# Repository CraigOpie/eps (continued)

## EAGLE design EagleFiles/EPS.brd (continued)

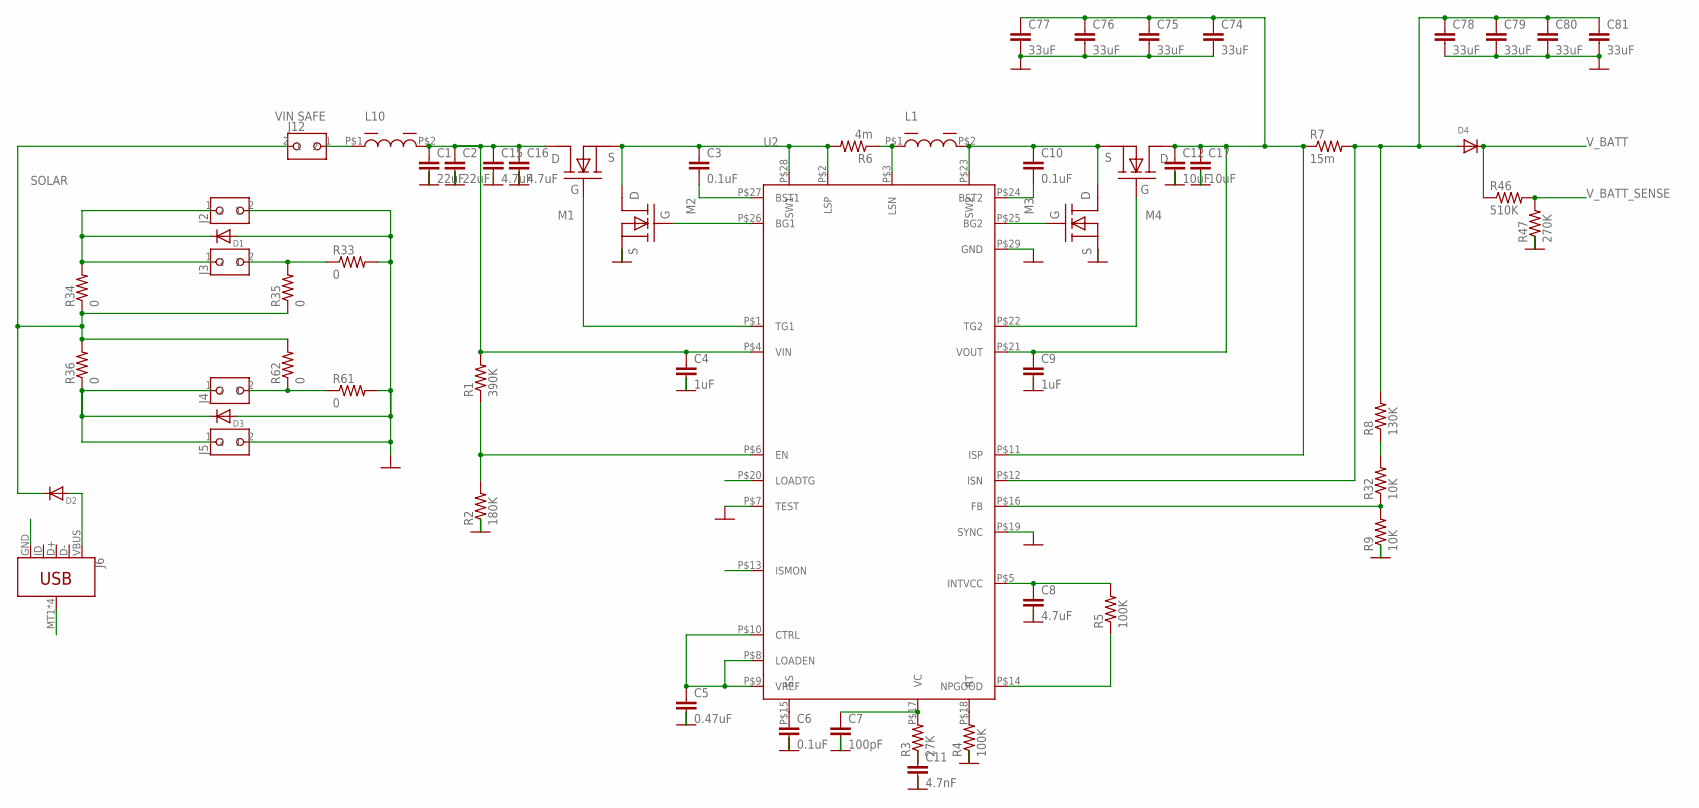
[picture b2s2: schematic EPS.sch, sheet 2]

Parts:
C1, C2: 22uF; 0805
C3, C6, C10: 0.1uF; 0805
C4, C9: 1uF; 0805
C5: 0.47uF; 0805
C7: 100pF; 0805
C8, C15, C16: 4.7uF; 0805
C11: 4.7nF; 0805
C12, C17: 10uF; 0805
C74, C75, C76, C77, C78, C79, C80, C81: 33uF; 1206
D1, D2, D3, D4: DIODE_SOD-123FL; SOD-123FL
J2, J3, J4, J5, J12: 2PIN_HEADER; 2MM_2PIN_HEADER
J6: USB_MICRO-B_SMT; USB-MICROB
L1, L10: 6uH; 7443551600
M1, M2: BSZ100N06LS3
M3, M4: BSZ033NE2LS5; BSZ100N06LS3
R1: 390K; 0805
R2: 180K; 0805
R3: 27K; 0805
R4, R5: 100K; 0805
R6: 4m; 0805
R7: 15m; 0805
R8: 130K; 0805
R9, R32: 10K; 0805
R33, R34, R35, R36, R61, R62: 0; 0603-RES
R46: 510K; 0805
R47: 270K; 0805
U2: LT8390UFD

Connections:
GND: C1.2, C2.2, C4.2, C5.2, C6.2, C7.2, C8.2, C9.2, C11.2, C12.2, C15.2, C16.2, C17.2, C74.2, C75.2, C76.2, C77.2, C78.2, C79.2, C80.2, C81.2, D1.A, D3.A, J2.2, J5.2, J6.GND, J6.MT1 (SHIELD), J6.MT2 (SHIELD), J6.P$1 (SHIELD), J6.P$2 (SHIELD), M2.P$2 (S), M2.P$3 (S), M2.P$4 (S), M3.P$2 (S), M3.P$3 (S), M3.P$4 (S), R2.1, R4.1, R9.1, R33.2, R47.1, R61.2, U2.P$7 (TEST), U2.P$19 (SYNC), U2.P$29 (GND); also elsewhere on the board
unnamed: C3.1, M1.P$2 (S), M1.P$3 (S), M1.P$4 (S), M2.P$5 (D), M2.P$6 (D), M2.P$7 (D), M2.P$8 (D), M2.P$9 (D), R6.2, U2.P$2 (LSP), U2.P$28 (SW1)
unnamed: C3.2, U2.P$27 (BST1)
unnamed: R8.1, R32.2
unnamed: M2.P$1 (G), U2.P$26 (BG1)
unnamed: M1.P$1 (G), U2.P$1 (TG1)
unnamed: M3.P$1 (G), U2.P$25 (BG2)
unnamed: R1.1, R2.2, U2.P$6 (EN)
unnamed: C5.1, U2.P$8 (LOADEN), U2.P$9 (VREF), U2.P$10 (CTRL)
unnamed: C6.1, U2.P$15 (SS)
unnamed: C7.1, R3.2, U2.P$17 (VC)
unnamed: R4.2, U2.P$18 (RT)
unnamed: R5.1, U2.P$14 (NPGOOD)
unnamed: C8.1, R5.2, U2.P$5 (INTVCC)
unnamed: L1.P$1, R6.1, U2.P$3 (LSN)
unnamed: C10.1, L1.P$2, M3.P$5 (D), M3.P$6 (D), M3.P$7 (D), M3.P$8 (D), M3.P$9 (D), M4.P$2 (S), M4.P$3 (S), M4.P$4 (S), U2.P$23 (SW2)
unnamed: C10.2, U2.P$24 (BST2)
unnamed: C9.1, C12.1, C17.1, C74.1, C75.1, C76.1, C77.1, M4.P$5 (D), M4.P$6 (D), M4.P$7 (D), M4.P$8 (D), M4.P$9 (D), R7.1, U2.P$11 (ISP), U2.P$21 (VOUT)
unnamed: M4.P$1 (G), U2.P$22 (TG2)
unnamed: J12.1, L10.P$1
unnamed: R9.2, R32.1, U2.P$16 (FB)
unnamed: D1.C, J2.1, J3.1, R34.2
unnamed: J3.2, R33.1, R35.2
unnamed: C11.1, R3.1
unnamed: J4.2, R61.1, R62.1
unnamed: D2.A, J6.VBUS
unnamed: C1.1, C2.1, C4.1, C15.1, C16.1, L10.P$2, M1.P$5 (D), M1.P$6 (D), M1.P$7 (D), M1.P$8 (D), M1.P$9 (D), R1.2, U2.P$4 (VIN)
unnamed: D3.C, J4.1, J5.1, R36.1
SOLAR: D2.C, J12.2, R34.1, R35.1, R36.2, R62.2
V_BATT: C78.1, C79.1, C80.1, C81.1, D4.A, D4.C, R7.2, R8.2, R46.1, U2.P$12 (ISN); also elsewhere on the board
V_BATT_SENSE: R46.2, R47.2; also elsewhere on the board

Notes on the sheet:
VIN SAFE

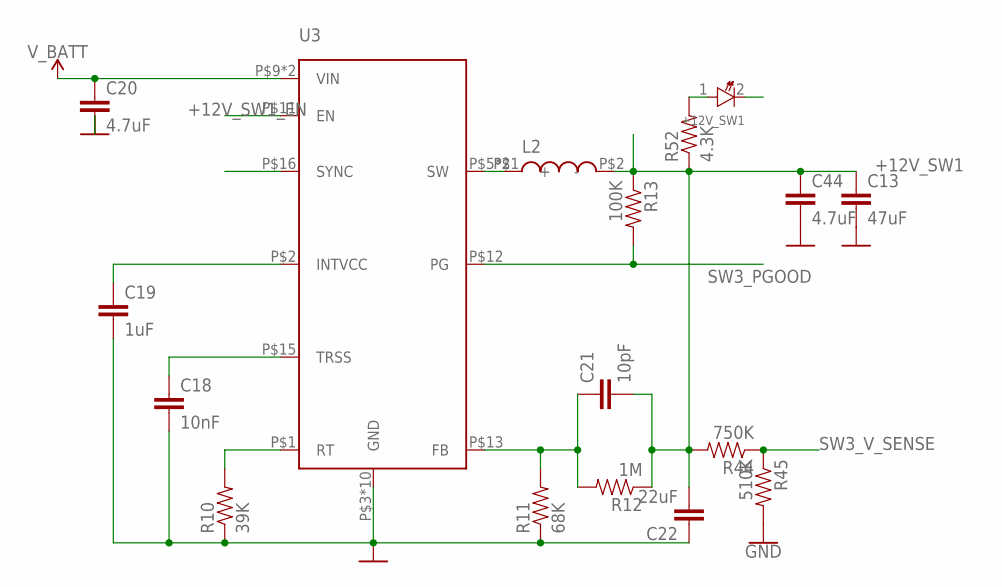
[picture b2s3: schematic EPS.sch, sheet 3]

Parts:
+12V_SW1: LED_0805
C13: 47uF; 1206
C18: 10nF; 0805
C19: 1uF; 0805
C20, C44: 4.7uF; 0805
C21: 10pF; 0805
C22: 22uF; 0805
L2: 10uH; XAL4040-103ME
R10: 39K; 0805
R11: 68K; 0805
R12: 1M; 0805
R13: 100K; 0805
R44: 750K; 0805
R45: 510K; 0805
R52: 4.3K; 0805
U3: LT8609S

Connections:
+12V_SW1: C13.1, C21.2, C22.2, C44.1, L2.P$2 (-), R12.1, R13.1, R44.2, R52.1; also elsewhere on the board
+12V_SW1_EN: U3.P$11 (EN); also elsewhere on the board
GND: +12V_SW1.2, C13.2, C18.2, C19.2, C20.2, C22.1, C44.2, R10.1, R11.1, R45.2, U3.P$3 (GND), U3.P$4 (GND), U3.P$7 (GND), U3.P$8 (GND), U3.P$14 (GND), U3.P$17 (GND), U3.P$18 (GND), U3.P$19 (GND), U3.P$20 (GND), U3.P$21 (GND); also elsewhere on the board
unnamed: L2.P$1 (+), U3.P$5 (SW), U3.P$6 (SW)
unnamed: R10.2, U3.P$1 (RT)
unnamed: C21.1, R11.2, R12.2, U3.P$13 (FB)
unnamed: C19.1, U3.P$2 (INTVCC)
unnamed: C18.1, U3.P$15 (TRSS)
unnamed: +12V_SW1.1, R52.2
SW3_PGOOD: R13.2, U3.P$12 (PG)
SW3_V_SENSE: R44.1, R45.1; also elsewhere on the board
V_BATT: C20.1, U3.P$9 (VIN), U3.P$10 (VIN); also elsewhere on the board

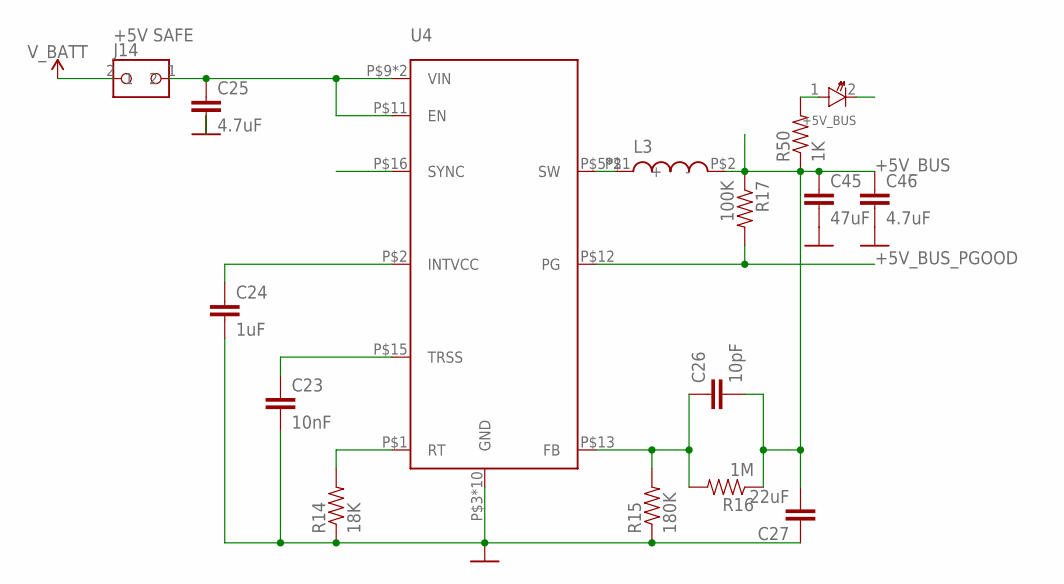
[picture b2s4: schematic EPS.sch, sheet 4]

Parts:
+5V_BUS: LED_0805
C23: 10nF; 0805
C24: 1uF; 0805
C25, C46: 4.7uF; 0805
C26: 10pF; 0805
C27: 22uF; 0805
C45: 47uF; 0805
J14: 2PIN_HEADER; 2MM_2PIN_HEADER
L3: 2.2uH; XAL4040-103ME
R14: 18K; 0805
R15: 180K; 0805
R16: 1M; 0805
R17: 100K; 0805
R50: 1K; 0805
U4: LT8609S

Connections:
+5V_BUS: C26.2, C27.2, C45.1, C46.1, L3.P$2 (-), R16.1, R17.1, R50.1; also elsewhere on the board
+5V_BUS_PGOOD: R17.2, U4.P$12 (PG)
GND: +5V_BUS.2, C23.2, C24.2, C25.2, C27.1, C45.2, C46.2, R14.1, R15.1, U4.P$3 (GND), U4.P$4 (GND), U4.P$7 (GND), U4.P$8 (GND), U4.P$14 (GND), U4.P$17 (GND), U4.P$18 (GND), U4.P$19 (GND), U4.P$20 (GND), U4.P$21 (GND); also elsewhere on the board
unnamed: R14.2, U4.P$1 (RT)
unnamed: C26.1, R15.2, R16.2, U4.P$13 (FB)
unnamed: C24.1, U4.P$2 (INTVCC)
unnamed: C23.1, U4.P$15 (TRSS)
unnamed: L3.P$1 (+), U4.P$5 (SW), U4.P$6 (SW)
unnamed: +5V_BUS.1, R50.2
V_BATT: J14.2; also elsewhere on the board
V_BUS: C25.1, J14.1, U4.P$9 (VIN), U4.P$10 (VIN), U4.P$11 (EN); also elsewhere on the board

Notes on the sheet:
+5V SAFE

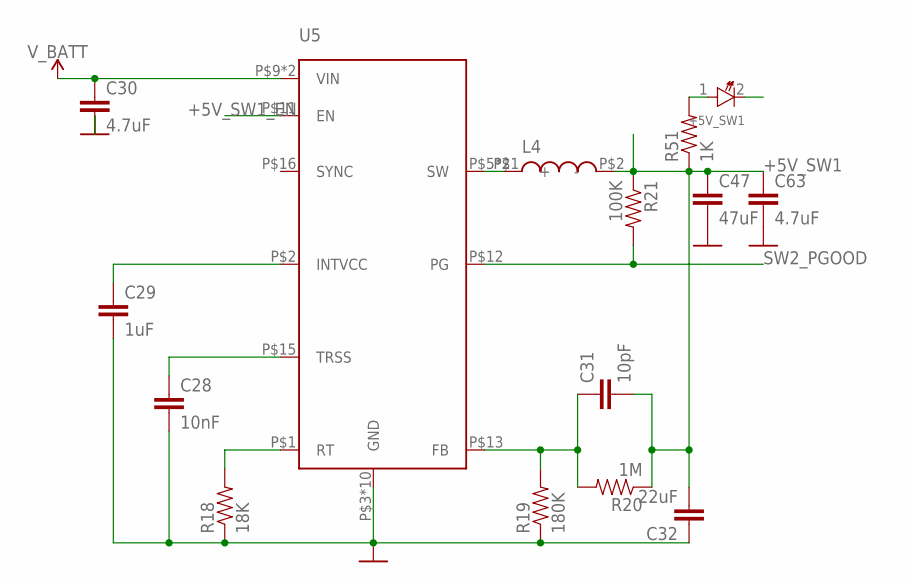
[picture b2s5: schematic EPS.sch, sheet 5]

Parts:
+5V_SW1: LED_0805
C28: 10nF; 0805
C29: 1uF; 0805
C30, C63: 4.7uF; 0805
C31: 10pF; 0805
C32: 22uF; 0805
C47: 47uF; 0805
L4: 2.2uH; XAL4040-103ME
R18: 18K; 0805
R19: 180K; 0805
R20: 1M; 0805
R21: 100K; 0805
R51: 1K; 0805
U5: LT8609S

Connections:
+5V_SW1: C31.2, C32.2, C47.1, C63.1, L4.P$2 (-), R20.1, R21.1, R51.1; also elsewhere on the board
+5V_SW1_EN: U5.P$11 (EN); also elsewhere on the board
GND: +5V_SW1.2, C28.2, C29.2, C30.2, C32.1, C47.2, C63.2, R18.1, R19.1, U5.P$3 (GND), U5.P$4 (GND), U5.P$7 (GND), U5.P$8 (GND), U5.P$14 (GND), U5.P$17 (GND), U5.P$18 (GND), U5.P$19 (GND), U5.P$20 (GND), U5.P$21 (GND); also elsewhere on the board
unnamed: R18.2, U5.P$1 (RT)
unnamed: C31.1, R19.2, R20.2, U5.P$13 (FB)
unnamed: C29.1, U5.P$2 (INTVCC)
unnamed: C28.1, U5.P$15 (TRSS)
unnamed: L4.P$1 (+), U5.P$5 (SW), U5.P$6 (SW)
unnamed: +5V_SW1.1, R51.2
SW2_PGOOD: R21.2, U5.P$12 (PG); also elsewhere on the board
V_BATT: C30.1, U5.P$9 (VIN), U5.P$10 (VIN); also elsewhere on the board

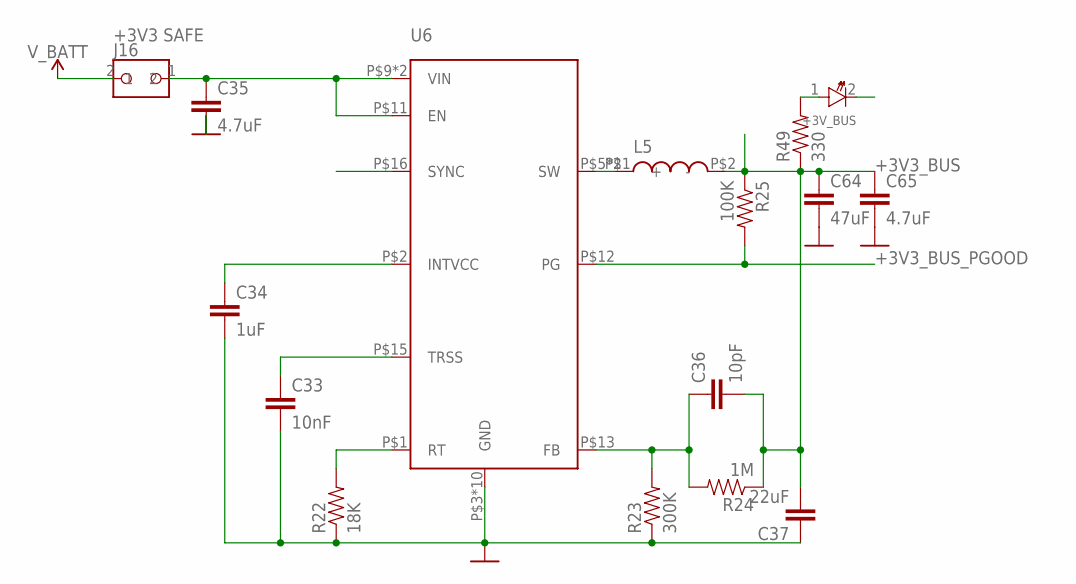
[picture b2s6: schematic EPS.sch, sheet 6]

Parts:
+3V_BUS: LED_0805
C33: 10nF; 0805
C34: 1uF; 0805
C35, C65: 4.7uF; 0805
C36: 10pF; 0805
C37: 22uF; 0805
C64: 47uF; 0805
J16: 2PIN_HEADER; 2MM_2PIN_HEADER
L5: 2.2uH; XAL4040-103ME
R22: 18K; 0805
R23: 300K; 0805
R24: 1M; 0805
R25: 100K; 0805
R49: 330; 0805
U6: LT8609S

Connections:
+3V3_BUS: C36.2, C37.2, C64.1, C65.1, L5.P$2 (-), R24.1, R25.1, R49.1; also elsewhere on the board
+3V3_BUS_PGOOD: R25.2, U6.P$12 (PG)
GND: +3V_BUS.2, C33.2, C34.2, C35.2, C37.1, C64.2, C65.2, R22.1, R23.1, U6.P$3 (GND), U6.P$4 (GND), U6.P$7 (GND), U6.P$8 (GND), U6.P$14 (GND), U6.P$17 (GND), U6.P$18 (GND), U6.P$19 (GND), U6.P$20 (GND), U6.P$21 (GND); also elsewhere on the board
unnamed: R22.2, U6.P$1 (RT)
unnamed: C36.1, R23.2, R24.2, U6.P$13 (FB)
unnamed: C34.1, U6.P$2 (INTVCC)
unnamed: C33.1, U6.P$15 (TRSS)
unnamed: L5.P$1 (+), U6.P$5 (SW), U6.P$6 (SW)
unnamed: +3V_BUS.1, R49.2
V_BATT: J16.2; also elsewhere on the board
V_BUS: C35.1, J16.1, U6.P$9 (VIN), U6.P$10 (VIN), U6.P$11 (EN); also elsewhere on the board

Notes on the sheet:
+3V3 SAFE

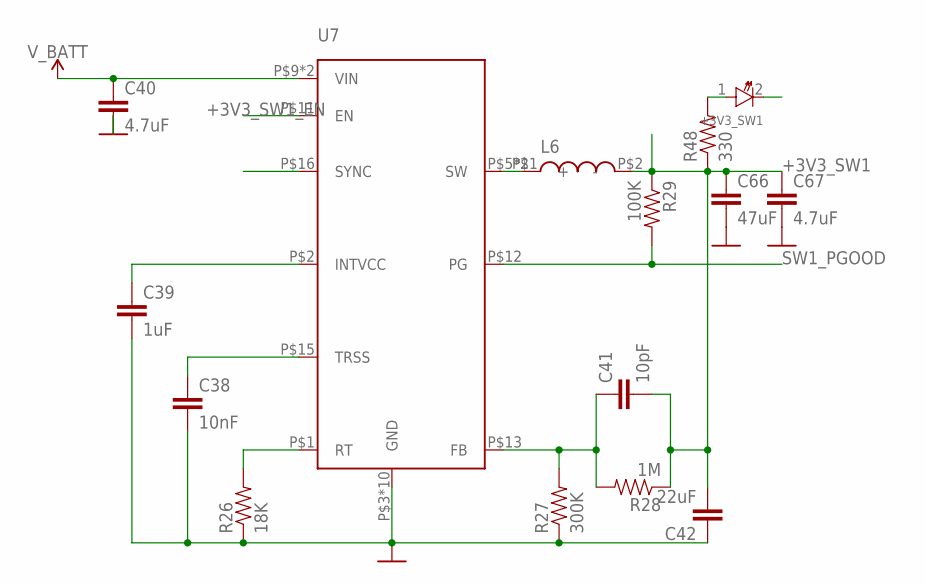
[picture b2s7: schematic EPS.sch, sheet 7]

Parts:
+3V3_SW1: LED_0805
C38: 10nF; 0805
C39: 1uF; 0805
C40, C67: 4.7uF; 0805
C41: 10pF; 0805
C42: 22uF; 0805
C66: 47uF; 0805
L6: 2.2uH; XAL4040-103ME
R26: 18K; 0805
R27: 300K; 0805
R28: 1M; 0805
R29: 100K; 0805
R48: 330; 0805
U7: LT8609S

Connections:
+3V3_SW1: C41.2, C42.2, C66.1, C67.1, L6.P$2 (-), R28.1, R29.1, R48.1; also elsewhere on the board
+3V3_SW1_EN: U7.P$11 (EN); also elsewhere on the board
GND: +3V3_SW1.2, C38.2, C39.2, C40.2, C42.1, C66.2, C67.2, R26.1, R27.1, U7.P$3 (GND), U7.P$4 (GND), U7.P$7 (GND), U7.P$8 (GND), U7.P$14 (GND), U7.P$17 (GND), U7.P$18 (GND), U7.P$19 (GND), U7.P$20 (GND), U7.P$21 (GND); also elsewhere on the board
unnamed: R26.2, U7.P$1 (RT)
unnamed: C41.1, R27.2, R28.2, U7.P$13 (FB)
unnamed: C39.1, U7.P$2 (INTVCC)
unnamed: C38.1, U7.P$15 (TRSS)
unnamed: L6.P$1 (+), U7.P$5 (SW), U7.P$6 (SW)
unnamed: +3V3_SW1.1, R48.2
SW1_PGOOD: R29.2, U7.P$12 (PG); also elsewhere on the board
V_BATT: C40.1, U7.P$9 (VIN), U7.P$10 (VIN); also elsewhere on the board

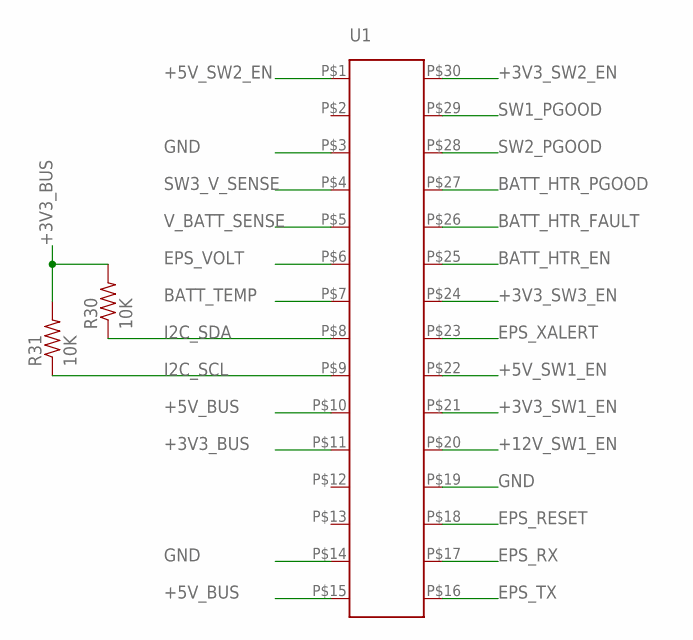
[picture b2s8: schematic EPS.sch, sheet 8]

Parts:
R30, R31: 10K; 0805
U1: ARDUINO_EVERY_NANO_PAD; ARDUINO_EVERY_NANO

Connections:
+3V3_BUS: R30.2, R31.2, U1.P$11; also elsewhere on the board
+3V3_SW1_EN: U1.P$21; also elsewhere on the board
+3V3_SW2_EN: U1.P$30; also elsewhere on the board
+3V3_SW3_EN: U1.P$24; also elsewhere on the board
+5V_BUS: U1.P$10, U1.P$15; also elsewhere on the board
+5V_SW1_EN: U1.P$22; also elsewhere on the board
+5V_SW2_EN: U1.P$1; also elsewhere on the board
+12V_SW1_EN: U1.P$20; also elsewhere on the board
BATT_HTR_EN: U1.P$25; also elsewhere on the board
BATT_HTR_FAULT: U1.P$26; also elsewhere on the board
BATT_HTR_PGOOD: U1.P$27; also elsewhere on the board
BATT_TEMP: U1.P$7; also elsewhere on the board
EPS_RESET: U1.P$18; also elsewhere on the board
EPS_RX: U1.P$17; also elsewhere on the board
EPS_TX: U1.P$16; also elsewhere on the board
EPS_VOLT: U1.P$6; also elsewhere on the board
EPS_XALERT: U1.P$23; also elsewhere on the board
GND: U1.P$3, U1.P$14, U1.P$19; also elsewhere on the board
I2C_SCL: R31.1, U1.P$9; also elsewhere on the board
I2C_SDA: R30.1, U1.P$8; also elsewhere on the board
SW1_PGOOD: U1.P$29; also elsewhere on the board
SW2_PGOOD: U1.P$28; also elsewhere on the board
SW3_V_SENSE: U1.P$4; also elsewhere on the board
V_BATT_SENSE: U1.P$5; also elsewhere on the board

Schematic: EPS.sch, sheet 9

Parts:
+5V_SW2: LED_0805
C48: 10nF; 0805
C49: 1uF; 0805
C50, C69: 4.7uF; 0805
C51: 10pF; 0805
C52: 22uF; 0805
C68: 47uF; 0805
L7: 2.2uH; XAL4040-103ME
R37: 18K; 0805
R38: 180K; 0805
R39: 1M; 0805
R40: 100K; 0805
R41: 1K; 0805
U8: LT8609S

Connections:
+5V_SW2: C51.2, C52.2, C68.1, C69.1, L7.P$2 (-), R39.1, R40.1, R41.1; also elsewhere on the board
+5V_SW2_EN: U8.P$11 (EN); also elsewhere on the board
+5V_SW2_PGOOD: R40.2, U8.P$12 (PG)
GND: +5V_SW2.2, C48.2, C49.2, C50.2, C52.1, C68.2, C69.2, R37.1, R38.1, U8.P$3 (GND), U8.P$4 (GND), U8.P$7 (GND), U8.P$8 (GND), U8.P$14 (GND), U8.P$17 (GND), U8.P$18 (GND), U8.P$19 (GND), U8.P$20 (GND), U8.P$21 (GND); also elsewhere on the board
unnamed: R37.2, U8.P$1 (RT)
unnamed: C51.1, R38.2, R39.2, U8.P$13 (FB)
unnamed: C49.1, U8.P$2 (INTVCC)
unnamed: C48.1, U8.P$15 (TRSS)
unnamed: L7.P$1 (+), U8.P$5 (SW), U8.P$6 (SW)
unnamed: +5V_SW2.1, R41.2
V_BATT: C50.1, U8.P$9 (VIN), U8.P$10 (VIN); also elsewhere on the board

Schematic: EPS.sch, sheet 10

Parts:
+3V3_SW2: LED_0805
C53: 10nF; 0805
C54: 1uF; 0805
C55, C71: 4.7uF; 0805
C56: 10pF; 0805
C57: 22uF; 0805
C70: 47uF; 0805
L8: 2.2uH; XAL4040-103ME
R42: 18K; 0805
R43: 300K; 0805
R53: 1M; 0805
R54: 100K; 0805
R55: 330; 0805
U9: LT8609S

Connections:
+3V3_SW2: C56.2, C57.2, C70.1, C71.1, L8.P$2 (-), R53.1, R54.1, R55.1; also elsewhere on the board
+3V3_SW2_EN: U9.P$11 (EN); also elsewhere on the board
+3V3_SW2_PGOOD: R54.2, U9.P$12 (PG)
GND: +3V3_SW2.2, C53.2, C54.2, C55.2, C57.1, C70.2, C71.2, R42.1, R43.1, U9.P$3 (GND), U9.P$4 (GND), U9.P$7 (GND), U9.P$8 (GND), U9.P$14 (GND), U9.P$17 (GND), U9.P$18 (GND), U9.P$19 (GND), U9.P$20 (GND), U9.P$21 (GND); also elsewhere on the board
unnamed: R42.2, U9.P$1 (RT)
unnamed: C56.1, R43.2, R53.2, U9.P$13 (FB)
unnamed: C54.1, U9.P$2 (INTVCC)
unnamed: C53.1, U9.P$15 (TRSS)
unnamed: L8.P$1 (+), U9.P$5 (SW), U9.P$6 (SW)
unnamed: +3V3_SW2.1, R55.2
V_BATT: C55.1, U9.P$9 (VIN), U9.P$10 (VIN); also elsewhere on the board

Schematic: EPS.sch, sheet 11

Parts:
+3V3_SW3: LED_0805
C58: 10nF; 0805
C59: 1uF; 0805
C60, C73: 4.7uF; 0805
C61: 10pF; 0805
C62: 22uF; 0805
C72: 47uF; 0805
L9: 2.2uH; XAL4040-103ME
R56: 18K; 0805
R57: 300K; 0805
R58: 1M; 0805
R59: 100K; 0805
R60: 330; 0805
U10: LT8609S

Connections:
+3V3_SW3: C61.2, C62.2, C72.1, C73.1, L9.P$2 (-), R58.1, R59.1, R60.1; also elsewhere on the board
+3V3_SW3_EN: U10.P$11 (EN); also elsewhere on the board
+3V3_SW3_PGOOD: R59.2, U10.P$12 (PG)
GND: +3V3_SW3.2, C58.2, C59.2, C60.2, C62.1, C72.2, C73.2, R56.1, R57.1, U10.P$3 (GND), U10.P$4 (GND), U10.P$7 (GND), U10.P$8 (GND), U10.P$14 (GND), U10.P$17 (GND), U10.P$18 (GND), U10.P$19 (GND), U10.P$20 (GND), U10.P$21 (GND); also elsewhere on the board
unnamed: R56.2, U10.P$1 (RT)
unnamed: C61.1, R57.2, R58.2, U10.P$13 (FB)
unnamed: C59.1, U10.P$2 (INTVCC)
unnamed: C58.1, U10.P$15 (TRSS)
unnamed: L9.P$1 (+), U10.P$5 (SW), U10.P$6 (SW)
unnamed: +3V3_SW3.1, R60.2
V_BATT: C60.1, U10.P$9 (VIN), U10.P$10 (VIN); also elsewhere on the board

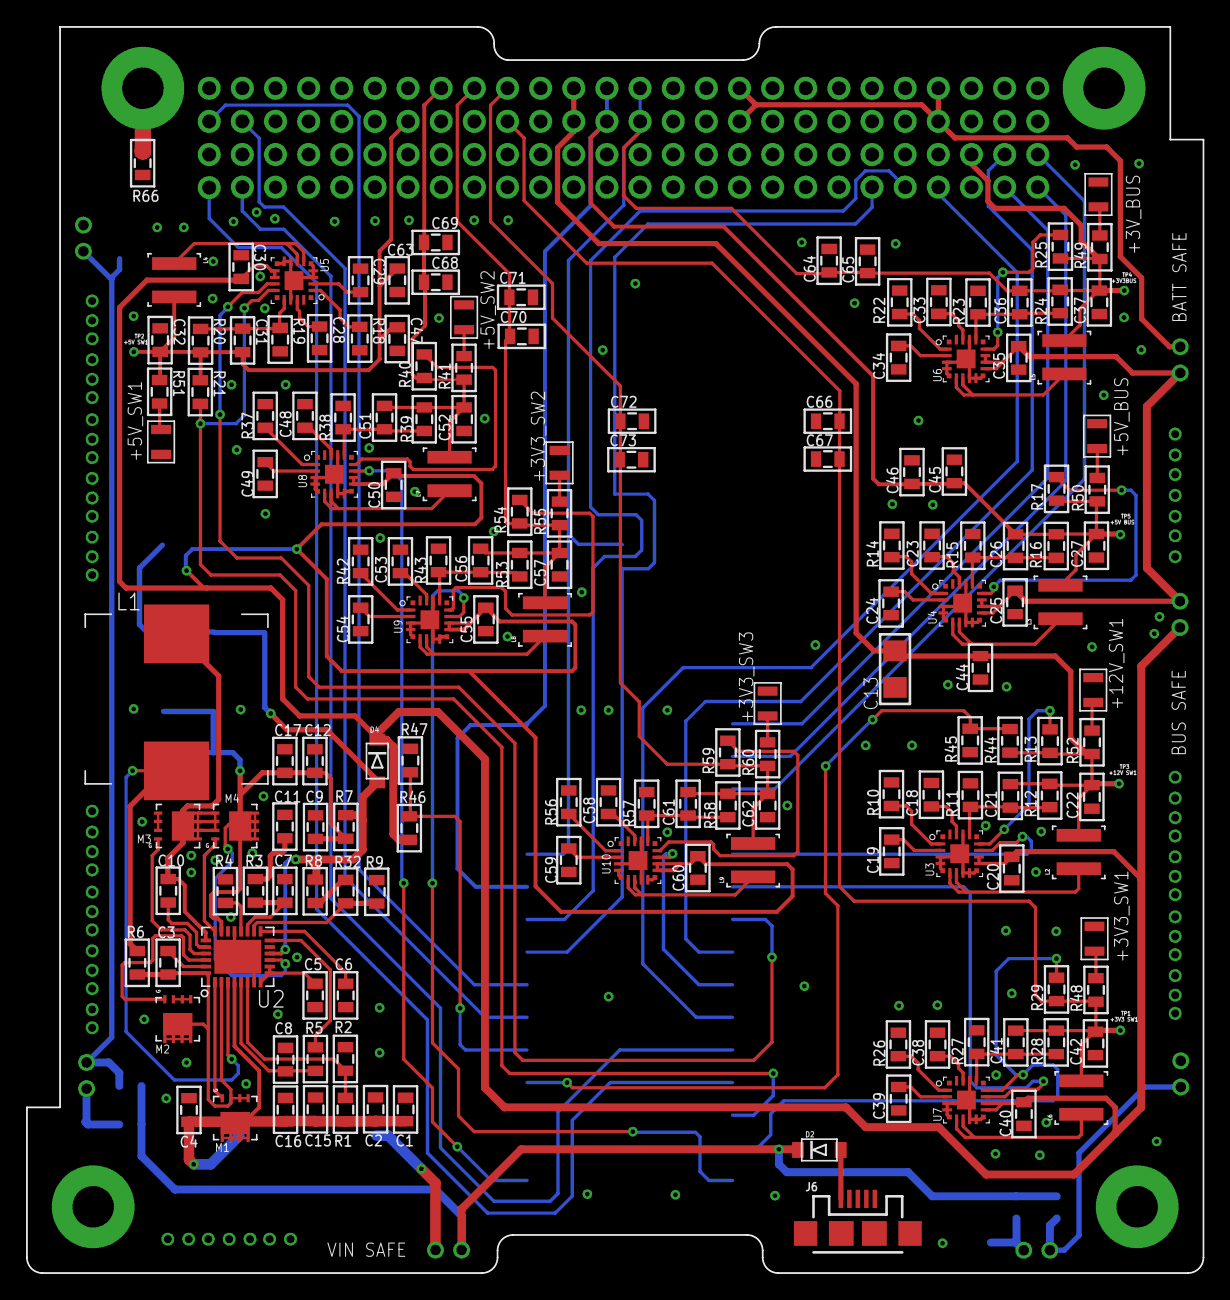
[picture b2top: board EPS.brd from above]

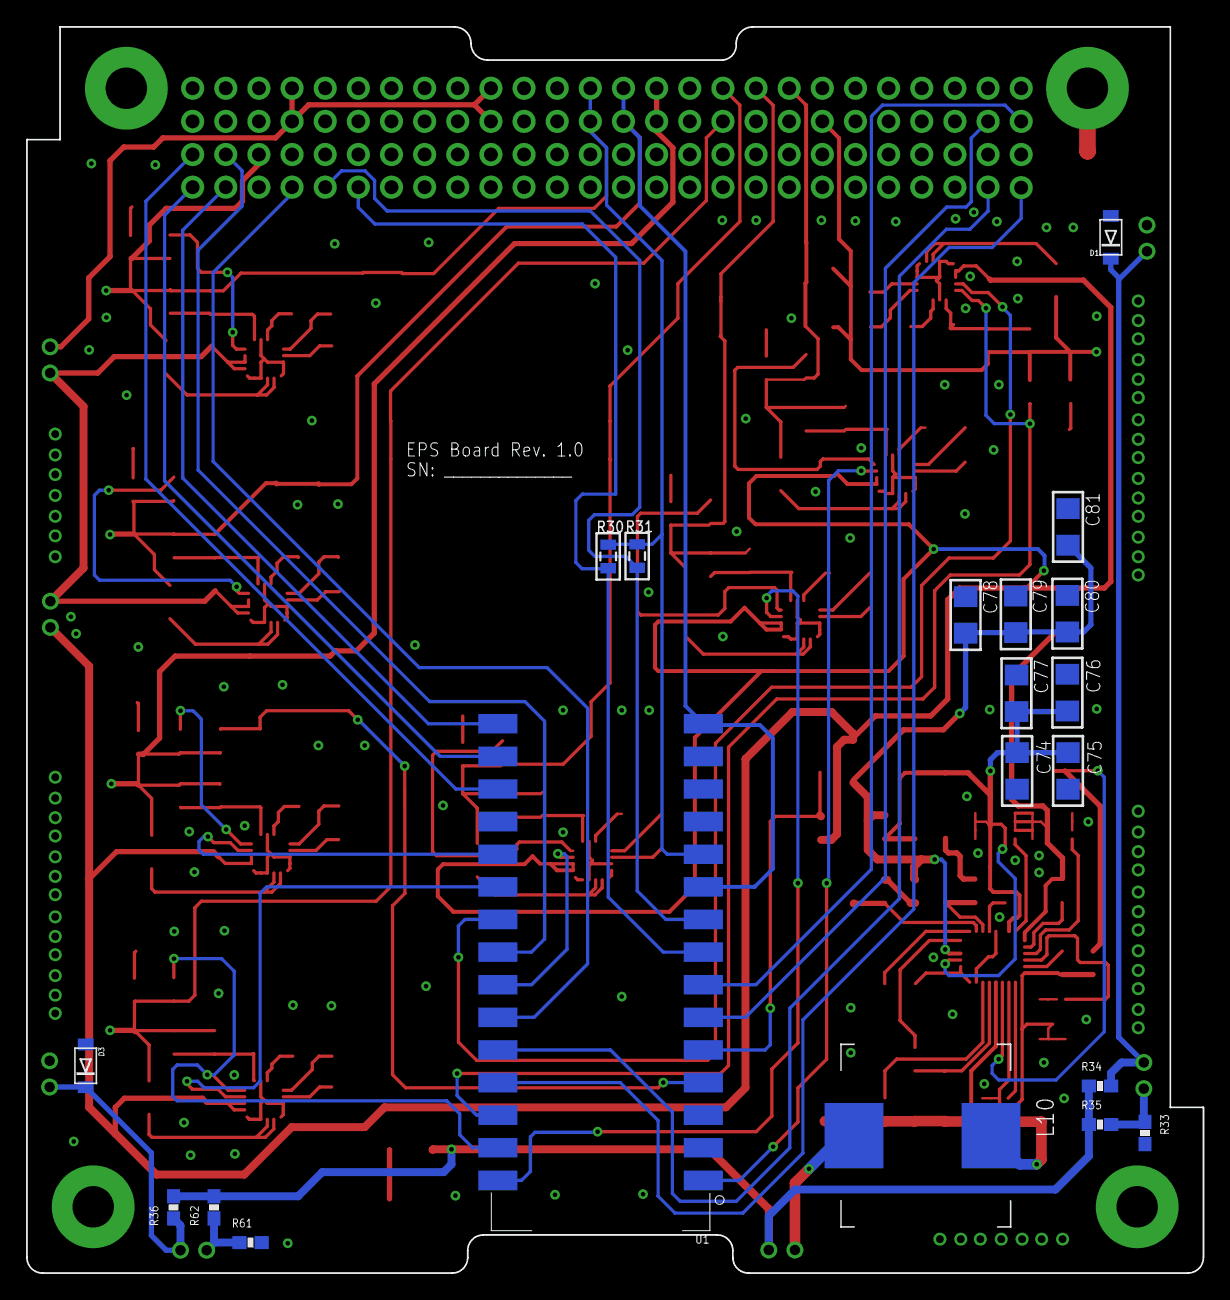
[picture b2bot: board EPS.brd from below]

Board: 2 copper layers, 90.2 x 95.5 mm, 187 parts (20 on the bottom side), 115 nets.

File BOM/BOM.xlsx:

Identifier | Value | Part Number | Quantity | Amplifying Info | DigiKey PN | Price | Total
12V_SW1, 5V_BUS, 5V_SW1, 5V_SW2, 3V3_BUS, 3V3_SW1, 3V3_SW2, 3V3_SW3 | GREEN | APHCM2012CGCK-F01 | 8.0 | 0805 LED | 754-1094-1-ND | 0.51 | 4.08
C1, C2 | 22uF | T529P226M010AAE200 | 2.0 | Must Be Low ESR, Tantalum (0805 Footprint) | 399-10534-1-ND | 1.35 | 2.7
C11 | 4.7nF | C0805C472K5RACTU | 1.0 |  | 399-1155-1-ND | 0.1 | 0.1
C12, C17 | 10uF | GRM21BR61E106MA73L | 2.0 |  | 490-10748-1-ND | 0.27 | 0.54
C74, C75, C76, C77, C78, C79, C80, C81 | 33uF | TCJA336M016R0200E | 8.0 | Must Be Low ESR, Tantalum (0805 Footprint) | 478-13504-1-ND | 0.84 | 6.72
C15, C16, C8, C20, C44, C25, C46, C30, C63, C35, C65, C40, C67, C50, C69, C55, 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 | 4.7uF | GRM219R61E475KA73D | 19.0 |  | 490-12753-1-ND | 0.27 | 5.13
C18, C23, C28, C33, C38, C48, C53, C58 | 10nF | C0805C103K1RAC7210 | 8.0 |  | 399-17617-1-ND | 0.1 | 0.8
C21, C26, C31, C36, C41, C51, C56, C61 | 10pF | C0805C100K5RAC7800 | 8.0 |  | 399-17612-1-ND | 0.26 | 2.08
C22, C27, C32, C37, C42, C52, C57, C62 | 22uF | GRM21BR61E226ME44K | 8.0 |  | 490-14661-1-ND | 0.49 | 3.92
C3, C10, C6 | 0.1uF | C0805C104M3RACTU | 3.0 |  | 399-8000-1-ND | 0.1 | 0.3
C4, C9, C19, C24, C29, C34, C39, C49, C54, C59 | 1uF | C0805C105K4RACTU | 10.0 |  | 399-1284-1-ND | 0.15 | 1.5
C13 | 47uF | GRM31CR61E476ME44L | 1.0 | 1206 footprint | 490-16268-1-ND | 1.03 | 1.03
C45, C47, C64, C66, C68, C70, C72 | 47uF | GRM21BR61A476ME15L | 7.0 |  | 490-9961-1-ND | 0.73 | 5.11
C5 | 0.47uF | CC0805KKX7R8BB474 | 1.0 |  | 311-1364-1-ND | 0.21 | 0.21
C7 | 100pF | C0805C101J5RAC7800 | 1.0 |  | 399-17420-1-ND | 0.18 | 0.18
D1, D2, D3, D4 |  | MBR2H100SFT3G | 5.0 |  | MBR2H100SFT3GOSCT-ND | 0.45 | 2.25
H1, H2 |  |  | 2.0 |  |  |  | 0
J12, J14, J16 |  | 5.5932023E8 | 3.0 | Wires use 513820200 (Molex 2mm 2pos) | WM12283-ND | 0.46 | 1.38
J2, J3, J4, J5 |  | 5.5932023E8 | 4.0 | Wires use 513820200 (Molex 2mm 2pos) | WM12283-ND | 0.46 | 1.84
J6 |  | 10118192-0001LF | 1.0 | Micro USB-B Connector | 609-4613-1-ND | 0.43 | 0.43
L1, L10 | 6uH | 7.4435516E9 | 2.0 | Wurth | 732-1129-1-ND | 3.27 | 6.54
L2 | 10uH | XAL4040-103ME | 1.0 | Mouser Only | 994-XAL4040-103MEC | 3.11 | 3.11
L3, L4, L5, L6, L7, L8, L9 | 2.2uH | XFL4020-222ME | 7.0 | Mouser Only | 994-XFL4020-222MEB | 2.13 | 14.91
M1, M2 |  | BSZ100N06LS3GATMA1 | 2.0 | Infineon | BSZ100N06LS3GATMA1CT-ND | 0.94 | 1.88
M3, M4 |  | BSZ033NE2LS5ATMA1 | 2.0 | Mouser Only, Infineon | 726-BSZ033NE2LS5ATMA | 0.93 | 1.86
R1 | 390K |  | 1.0 |  |  |  | 0
R10 | 39K |  | 1.0 |  |  |  | 0
R11 | 68K |  | 1.0 |  |  |  | 0
R14, R18, R22, R26, R37, R42, R56 | 18K |  | 7.0 |  |  |  | 0
R2, R15, R19, R38 | 180K |  | 4.0 |  |  |  | 0
R23, R27, R43, R57 | 300K |  | 4.0 |  |  |  | 0
R3 | 27K |  | 1.0 |  |  |  | 0
R30, R31 | 10K | DNP | 2.0 | 100KHz I2C |  |  | 0
R9, R32 | 10K |  | 2.0 |  |  |  | 0
R4, R5, R13, R17, R21, R25, R29, R40, R54, R59 | 100K |  | 10.0 |  |  |  | 0
R44 | 750K |  | 1.0 |  |  |  | 0
R46, R45 | 510K |  | 2.0 |  |  |  | 0
R47 | 270K |  | 1.0 |  |  |  | 0
R49, R48, R55, R60 | 330.0 |  | 4.0 |  |  |  | 0
R50, R51, R41 | 1K |  | 3.0 |  |  |  | 0
R52 | 4.3K |  | 1.0 |  |  |  | 0
R6 | 4m | KRL2012E-M-R004-F-T5 | 1.0 |  | 408-1594-1-ND | 0.63 | 0.63
R66, R12, R16, R20, R24, R28, R39, R53, R58 | 1M |  | 9.0 |  |  |  | 0
R7 | 15m | KRL2012E-M-R015-F-T5 | 1.0 |  | 408-1601-1-ND | 0.63 | 0.63
R8 | 130K |  | 1.0 |  |  |  | 0
R33, R34, R35, R36, R61, R62 | 0.0 | 5110.0 | 6.0 | 1/2 Watt (Should just use copper braid) | 36-5110CT-ND | 0.43 | 2.58
U1 |  | 7.60049201477E11 | 1.0 | Arduino Nano Every |  | 9.9 | 9.9
U2 |  | LT8390HUFD#PBF | 1.0 |  | LT8390HUFD#PBF-ND | 13.01 | 13.01
U3, U4, U5, U6, U7, U8, U9, U10 |  | LT8609SIV#PBF | 8.0 |  | LT8609SIV#PBF-ND | 7.34 | 58.72
 |  |  |  |  |  | Grand Total | 154.07

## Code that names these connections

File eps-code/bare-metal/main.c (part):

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#define GET_PDMS_EXPECTED                     0x43
#define SET_PDM_ON                            0x50
#define SET_PDM_OFF                           0x51
#define EPS_RESET                             0x80
#define MAX_I2C_BYTES                         16

// PIN definitions
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    PMC_PCER0 = 1 << ID_PIOC;
    PMC_PCER0 = 1 << ID_PIOD;
    
    // PA17 (Peripheral A)
    PIOA->PIO_ABSR = 0 << TWD0;
    PIOA->PIO_PER = 0 << TWD0;
    PIOA->PIO_PDR = 1 << TWD0;
    
    // PA18 (Peripheral A)
    PIOA->PIO_ABSR = 0 << TWCK0;
    PIOC->PIO_PER = 0 << TWCK0;
    PIOA->PIO_PDR = 1 << TWCK0;

    // PC28 (LOW)
    PIOC->PIO_PER = 1 << I2C_ENABLE;
    PIOC->PIO_OER = 1 << I2C_ENABLE;
    PIOC->PIO_OWER = 1 << I2C_ENABLE;
    PIOC->PIO_CODR = 1 << I2C_ENABLE;
    
    // PA29 (LOW)
    PIOA->PIO_PER = 1 << VBAT_ENABLE;
    PIOA->PIO_OER = 1 << VBAT_ENABLE;
    PIOA->PIO_OWER = 1 << VBAT_ENABLE;
    PIOA->PIO_CODR = 1 << VBAT_ENABLE;
    
    // PC25 (LOW)
    PIOC->PIO_PER = 1 << SW1_ENABLE;
    PIOC->PIO_OER = 1 << SW1_ENABLE;
    PIOC->PIO_OWER = 1 << SW1_ENABLE;
    PIOC->PIO_CODR = 1 << SW1_ENABLE;
    
    // PC24 (LOW)
    PIOC->PIO_PER = 1 << SW2_ENABLE;
    PIOC->PIO_OER = 1 << SW2_ENABLE;
    PIOC->PIO_OWER = 1 << SW2_ENABLE;
    PIOC->PIO_CODR = 1 << SW2_ENABLE;
    
    // PC23 (LOW)
    PIOC->PIO_PER = 1 << SW3_ENABLE;
    PIOC->PIO_OER = 1 << SW3_ENABLE;
    PIOC->PIO_OWER = 1 << SW3_ENABLE;
    PIOC->PIO_CODR = 1 << SW3_ENABLE;
    
    // PC22 (LOW)
    PIOC->PIO_PER = 1 << SW4_ENABLE;
    PIOC->PIO_OER = 1 << SW4_ENABLE;
    PIOC->PIO_OWER = 1 << SW4_ENABLE;
    PIOC->PIO_CODR = 1 << SW4_ENABLE;
    
    // PC21 (LOW)
    PIOC->PIO_PER = 1 << SW5_ENABLE;
    PIOC->PIO_OER = 1 << SW5_ENABLE;
    PIOC->PIO_OWER = 1 << SW5_ENABLE;
    PIOC->PIO_CODR = 1 << SW5_ENABLE;
    
    // PB25 (HIGH)
    PIOB->PIO_PER = 1 << WDT_RESET;
    PIOB->PIO_OER = 1 << WDT_RESET;
    PIOB->PIO_OWER = 1 << WDT_RESET;
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
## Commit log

2020-11-30 init commit
2020-11-30 merged with v0.4.0
2020-11-30 Update LICENSE
2021-01-22 verified working
2021-01-22 synced files
2021-01-29 fixed BCR
2021-01-29 improved bare-metal code
2021-02-02 added a lot of files
2021-02-03 fixed SAM code
2021-02-03 updated readme and license
